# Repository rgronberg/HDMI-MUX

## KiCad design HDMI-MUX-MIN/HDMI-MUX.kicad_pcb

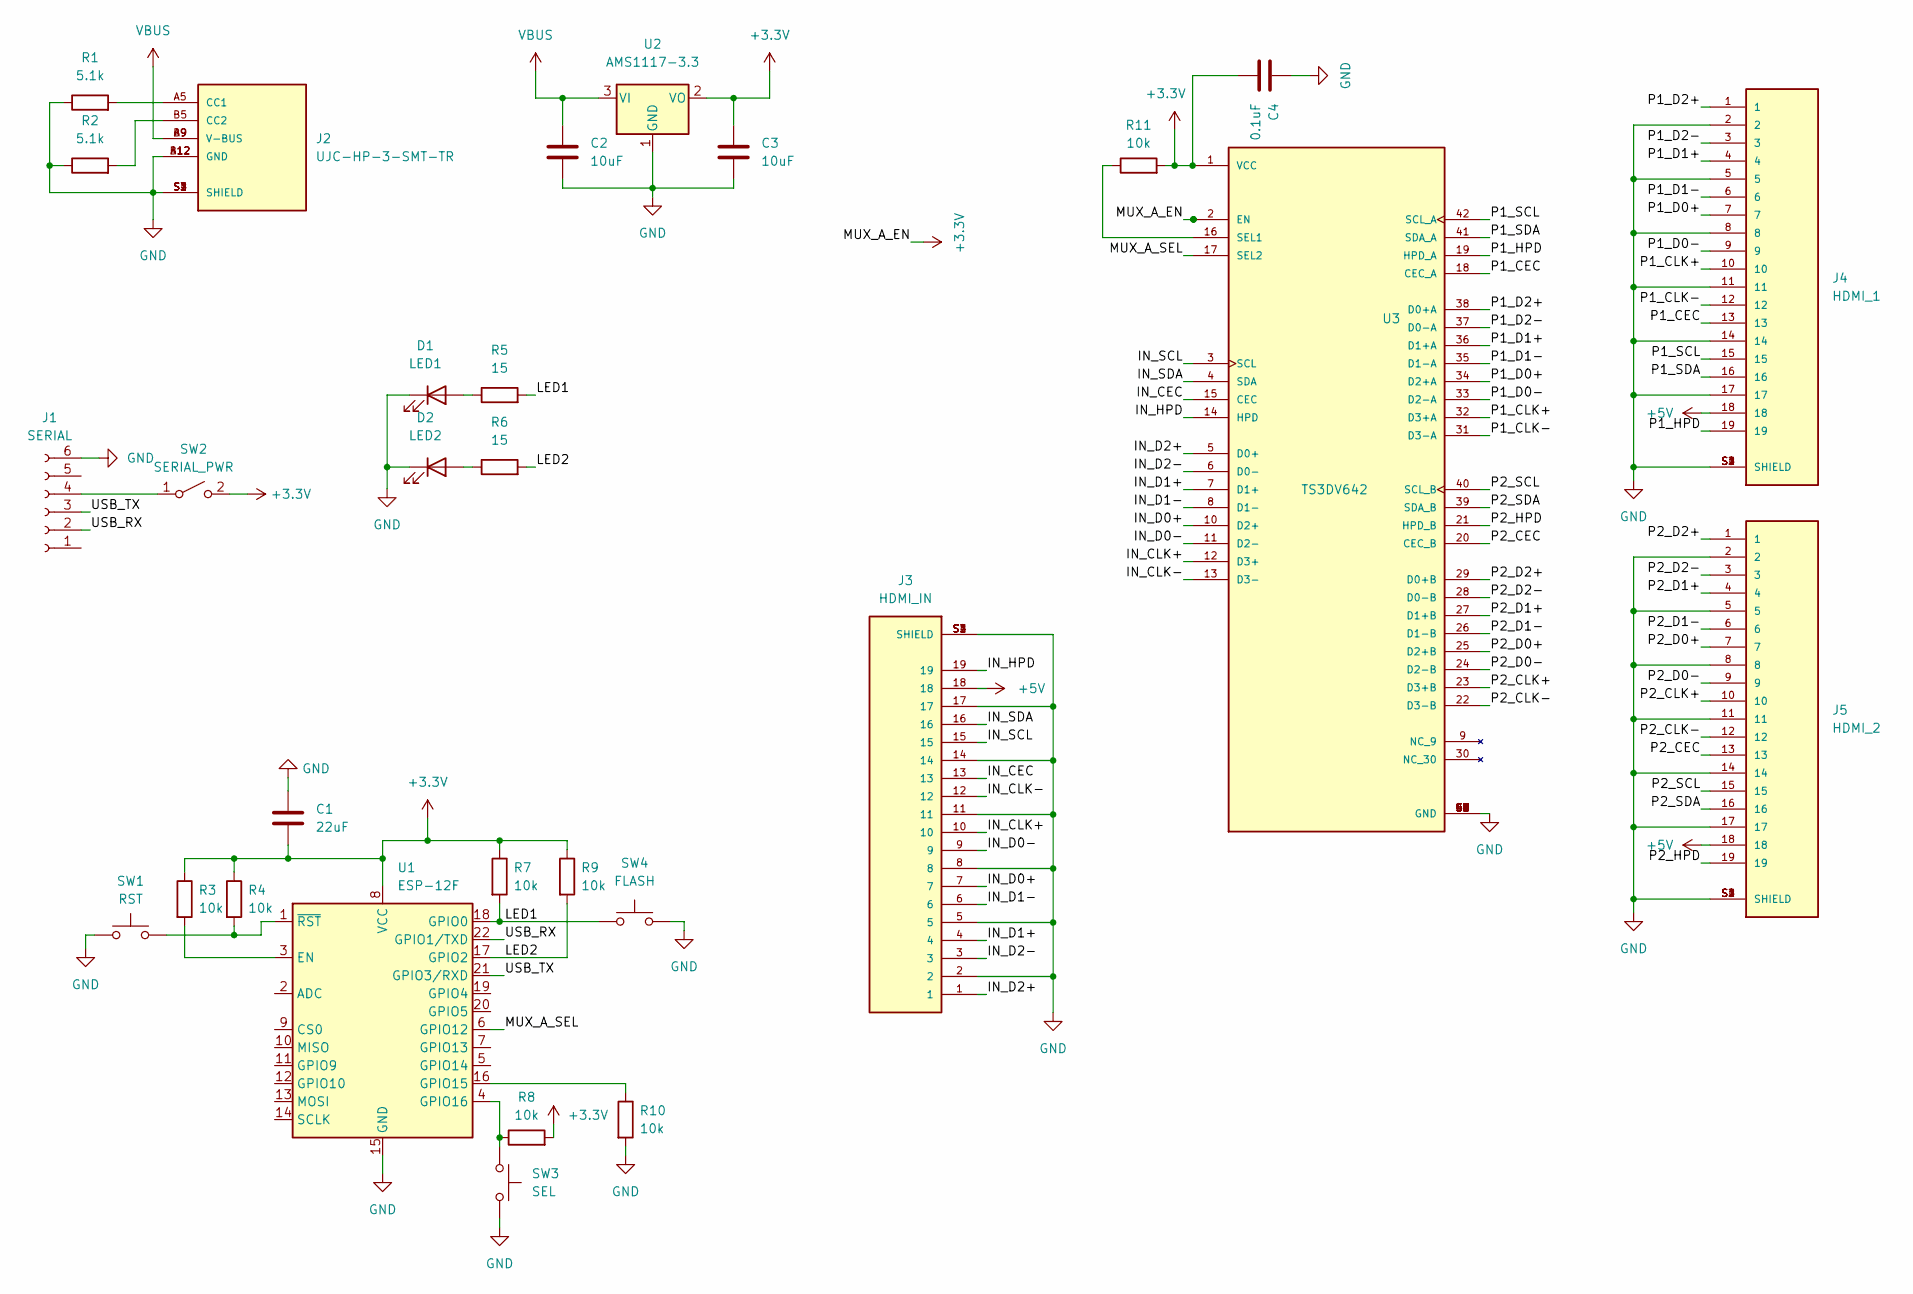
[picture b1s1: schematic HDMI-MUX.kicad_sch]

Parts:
C1: 22uF; C_0603_1608Metric_Pad1.08x0.95mm_HandSolder
C2, C3: 10uF; C_0603_1608Metric_Pad1.08x0.95mm_HandSolder
C4: 0.1uF; C_0603_1608Metric_Pad1.08x0.95mm_HandSolder
D1: LED1; LED_0805_2012Metric_Pad1.15x1.40mm_HandSolder
D2: LED2; LED_0805_2012Metric_Pad1.15x1.40mm_HandSolder
J1: SERIAL; PinSocket_1x06_P2.54mm_Vertical
J2: UJC-HP-3-SMT-TR; CUI_UJC-HP-3-SMT-TR; PARTREV 04/30/2020
J3: HDMI_IN; STEWART_SS-53000-001; PARTREV A0
J4: HDMI_1; STEWART_SS-53000-001; PARTREV A0
J5: HDMI_2; STEWART_SS-53000-001; PARTREV A0
R1, R2: 5.1k; R_0805_2012Metric_Pad1.20x1.40mm_HandSolder
R3, R4, R7, R8, R9, R10, R11: 10k; R_0805_2012Metric_Pad1.20x1.40mm_HandSolder
R5, R6: 15; R_0805_2012Metric_Pad1.20x1.40mm_HandSolder
SW1: RST; SW_PUSH_6mm
SW2: SERIAL_PWR; MINI-SPDT-SW
SW3: SEL; SW_PUSH_6mm
SW4: FLASH; SW_PUSH_6mm
U1: ESP-12F; ESP-12E
U2: AMS1117-3.3; SOT-223-3_TabPin2
U3: TS3DV642; QFN50P900X350X80-43N; PARTREV 4219139/A 03/2020

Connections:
+5V: J3.18, J4.18, J5.18
/IN_CEC: J3.13, U3.15 (CEC)
/IN_CLK+: J3.10, U3.12 (D3+)
/IN_CLK-: J3.12, U3.13 (D3-)
/IN_D0+: J3.7, U3.10 (D2+)
/IN_D0-: J3.9, U3.11 (D2-)
/IN_D1+: J3.4, U3.7 (D1+)
/IN_D1-: J3.6, U3.8 (D1-)
/IN_D2+: J3.1, U3.5 (D0+)
/IN_D2-: J3.3, U3.6 (D0-)
/IN_HPD: J3.19, U3.14 (HPD)
/IN_SCL: J3.15, U3.3 (SCL)
/IN_SDA: J3.16, U3.4 (SDA)
/LED1: R5.2, R7.2, SW4.1, U1.18 (GPIO0)
/LED2: R6.2, R9.2, U1.17 (GPIO2)
/MUX_A_SEL: U1.6 (GPIO12), U3.17 (SEL2)
/P1_CEC: J4.13, U3.18 (CEC_A)
/P1_CLK+: J4.10, U3.32 (D3+A)
/P1_CLK-: J4.12, U3.31 (D3-A)
/P1_D0+: J4.7, U3.34 (D2+A)
/P1_D0-: J4.9, U3.33 (D2-A)
/P1_D1+: J4.4, U3.36 (D1+A)
/P1_D1-: J4.6, U3.35 (D1-A)
/P1_D2+: J4.1, U3.38 (D0+A)
/P1_D2-: J4.3, U3.37 (D0-A)
/P1_HPD: J4.19, U3.19 (HPD_A)
/P1_SCL: J4.15, U3.42 (SCL_A)
/P1_SDA: J4.16, U3.41 (SDA_A)
/P2_CEC: J5.13, U3.20 (CEC_B)
/P2_CLK+: J5.10, U3.23 (D3+B)
/P2_CLK-: J5.12, U3.22 (D3-B)
/P2_D0+: J5.7, U3.25 (D2+B)
/P2_D0-: J5.9, U3.24 (D2-B)
/P2_D1+: J5.4, U3.27 (D1+B)
/P2_D1-: J5.6, U3.26 (D1-B)
/P2_D2+: J5.1, U3.29 (D0+B)
/P2_D2-: J5.3, U3.28 (D0-B)
/P2_HPD: J5.19, U3.21 (HPD_B)
/P2_SCL: J5.15, U3.40 (SCL_B)
/P2_SDA: J5.16, U3.39 (SDA_B)
/USB_RX: J1.2, U1.22 (GPIO1/TXD)
/USB_TX: J1.3, U1.21 (GPIO3/RXD)
GND: C1.1, C2.2, C3.2, C4.1, D1.1 (K), D2.1 (K), J1.6, J2.A12 (GND), J2.B12 (GND), J2.S1 (SHIELD), J2.S2 (SHIELD), J2.S3 (SHIELD), J2.S4 (SHIELD), J3.2, J3.5, J3.8, J3.11, J3.14, J3.17, J3.S1 (SHIELD), J3.S2 (SHIELD), J3.S3 (SHIELD), J3.S4 (SHIELD), J4.2, J4.5, J4.8, J4.11, J4.14, J4.17, J4.S1 (SHIELD), J4.S2 (SHIELD), J4.S3 (SHIELD), J4.S4 (SHIELD), J5.2, J5.5, J5.8, J5.11, J5.14, J5.17, J5.S1 (SHIELD), J5.S2 (SHIELD), J5.S3 (SHIELD), J5.S4 (SHIELD), R1.1, R2.1, R10.2, SW1.1, SW3.2, SW4.2, U1.15 (GND), U2.1 (GND), U3.43 (GND), U3.44 (GND), U3.45 (GND), U3.46 (GND), U3.47 (GND), U3.48 (GND), U3.49 (GND), U3.50 (GND), U3.51 (GND), U3.52 (GND), U3.53 (GND), U3.54 (GND), U3.55 (GND), U3.56 (GND), U3.57 (GND), U3.58 (GND), U3.59 (GND), U3.60 (GND)
unnamed: D1.2 (A), R5.1
unnamed: D2.2 (A), R6.1
unnamed: J1.4, SW2.1 (A)
unnamed: J2.A5 (CC1), R1.2
unnamed: J2.B5 (CC2), R2.2
unnamed: R3.2, U1.3 (EN)
unnamed: R4.2, SW1.2, U1.1 (~RST)
unnamed: R8.1, SW3.1, U1.4 (GPIO16)
unnamed: R10.1, U1.16 (GPIO15)
unnamed: R11.1, U3.16 (SEL1)
VBUS: C2.1, J2.A9 (V-BUS), J2.B9 (V-BUS), U2.3 (VI)

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
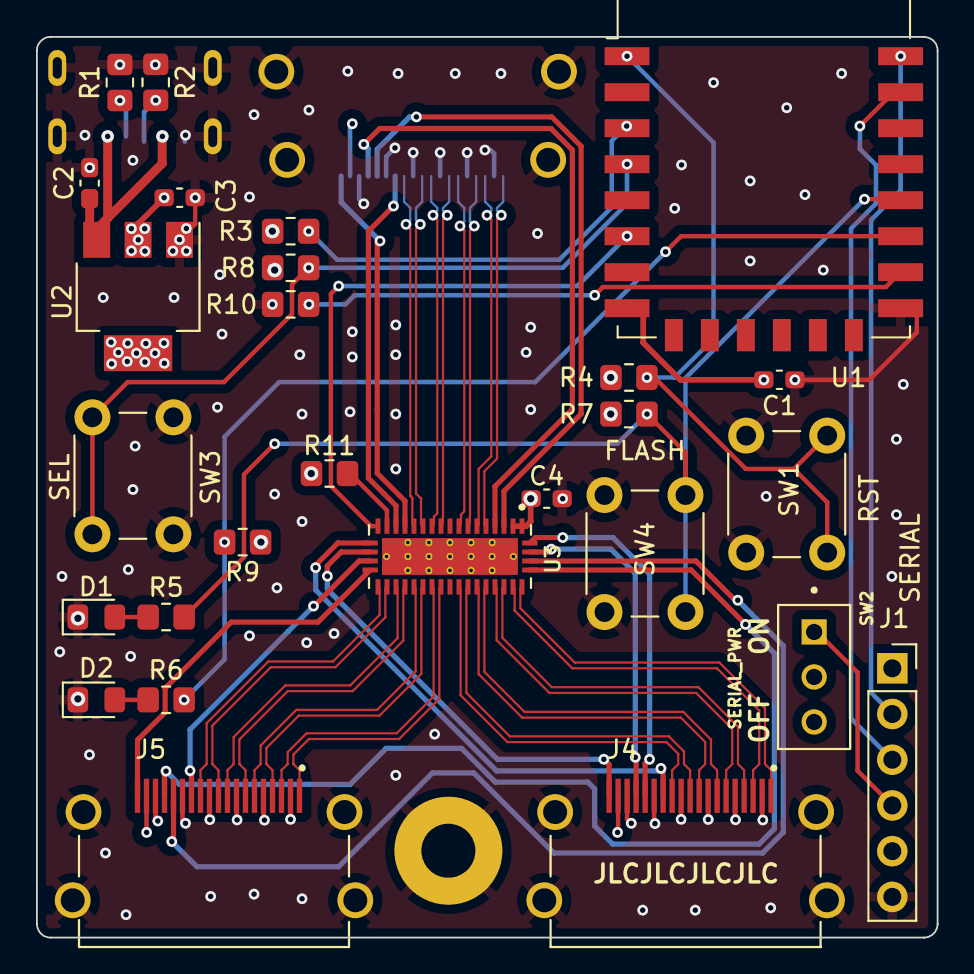
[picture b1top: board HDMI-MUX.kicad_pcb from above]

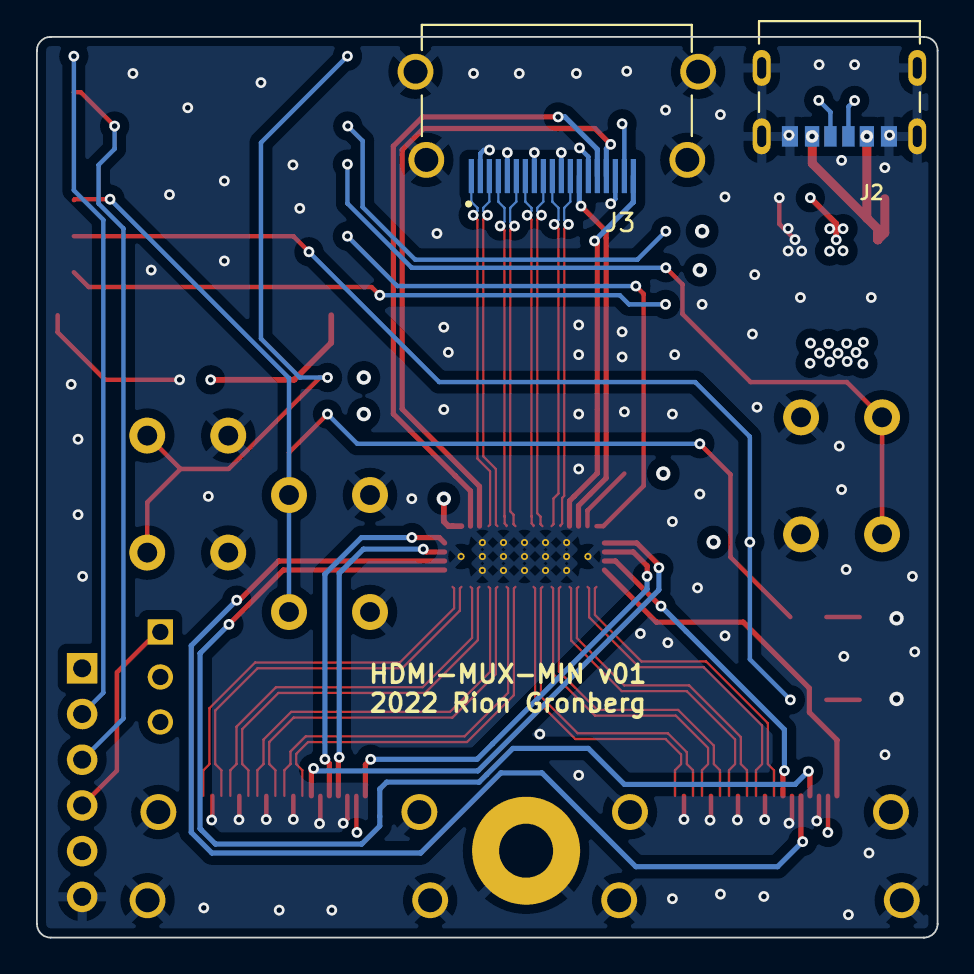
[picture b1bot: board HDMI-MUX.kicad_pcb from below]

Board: 4 copper layers, 50.0 x 50.0 mm, 29 parts (2 on the bottom side), 55 nets.

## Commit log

2022-07-26 Initial commit
    HDMI-MUX pcb completed at v01
    HDMI-MUX-driver in rough POC state
2022-07-28 Complete MuxDriver class
2022-07-28 Initial WebServer class
2022-07-31 Fix selected port reporting
2022-07-31 Update platform and add LittleFS
2022-07-31 Add html/js/css files to webserver
2022-07-31 Cleanup in WebServer class
2022-07-31 Enable long button press reset settings
2022-07-31 Cleanup in MuxDriver class
2022-07-31 Add NetBIOS support for hostname in windows
2022-07-31 Save selected port in EEPROM
2024-11-20 Update fab output
2024-11-20 Add in HDMI-MUX-MIN
